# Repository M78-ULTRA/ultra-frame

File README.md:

# ULTRA FRAME

Open source hardware and design files for a **leverless controller**— arcade-style input without a joystick gate, built for fighting games and anyone who prefers all-button layouts.

This repository is **work in progress**. KiCad projects, mechanical CAD, firmware, and documentation will land here as the design matures. Watch this space or star the repo if you want to follow along.

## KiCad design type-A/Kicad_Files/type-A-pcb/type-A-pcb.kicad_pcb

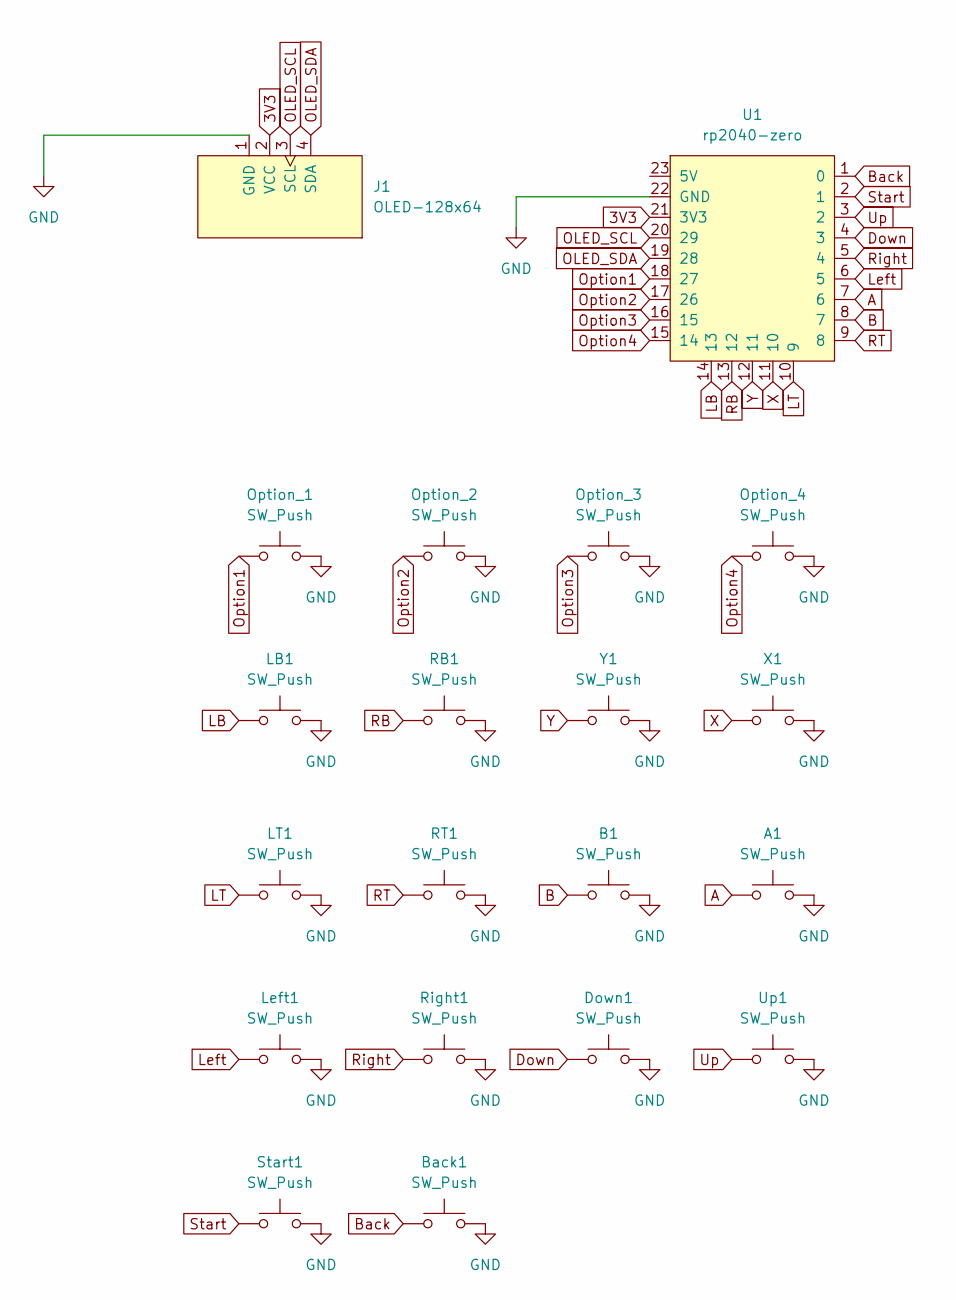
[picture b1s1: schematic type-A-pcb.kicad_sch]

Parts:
A1: SW_Push; Kailh_socket_PG1350_optional
B1: SW_Push; Kailh_socket_PG1350_optional
Back1: SW_Push; Kailh_socket_PG1350_optional
Down1: SW_Push; Kailh_socket_PG1350_optional
J1: OLED-128x64
LB1: SW_Push; Kailh_socket_PG1350_optional
LT1: SW_Push; Kailh_socket_PG1350_optional
Left1: SW_Push; Kailh_socket_PG1350_optional
Option_1, Option_2, Option_3, Option_4: SW_Push; Kailh_socket_PG1350_optional
RB1: SW_Push; Kailh_socket_PG1350_optional
RT1: SW_Push; Kailh_socket_PG1350_optional
Right1: SW_Push; Kailh_socket_PG1350_optional
Start1: SW_Push; Kailh_socket_PG1350_optional
U1: rp2040-zero; RP2040-Zero-Pretty
Up1: SW_Push; Kailh_socket_PG1350_optional
X1: SW_Push; Kailh_socket_PG1350_optional
Y1: SW_Push; Kailh_socket_PG1350_optional

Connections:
3V3: J1.2 (VCC), U1.21 (3V3)
A: A1.1, U1.7 (6)
B: B1.1, U1.8 (7)
Back: Back1.1, U1.1 (0)
Down: Down1.1, U1.4 (3)
GND: A1.2, B1.2, Back1.2, Down1.2, J1.1 (GND), LB1.2, LT1.2, Left1.2, Option_1.2, Option_2.2, Option_3.2, Option_4.2, RB1.2, RT1.2, Right1.2, Start1.2, U1.22 (GND), Up1.2, X1.2, Y1.2
LB: LB1.1, U1.14 (13)
LT: LT1.1, U1.10 (9)
Left: Left1.1, U1.6 (5)
OLED_SCL: J1.3 (SCL), U1.20 (29)
OLED_SDA: J1.4 (SDA), U1.19 (28)
Option1: Option_1.1, U1.18 (27)
Option2: Option_2.1, U1.17 (26)
Option3: Option_3.1, U1.16 (15)
Option4: Option_4.1, U1.15 (14)
RB: RB1.1, U1.13 (12)
RT: RT1.1, U1.9 (8)
Right: Right1.1, U1.5 (4)
Start: Start1.1, U1.2 (1)
Up: U1.3 (2), Up1.1
X: U1.11 (10), X1.1
Y: U1.12 (11), Y1.1

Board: 2 copper layers, 19 parts (0 on the bottom side), 19 nets, no tracks yet.

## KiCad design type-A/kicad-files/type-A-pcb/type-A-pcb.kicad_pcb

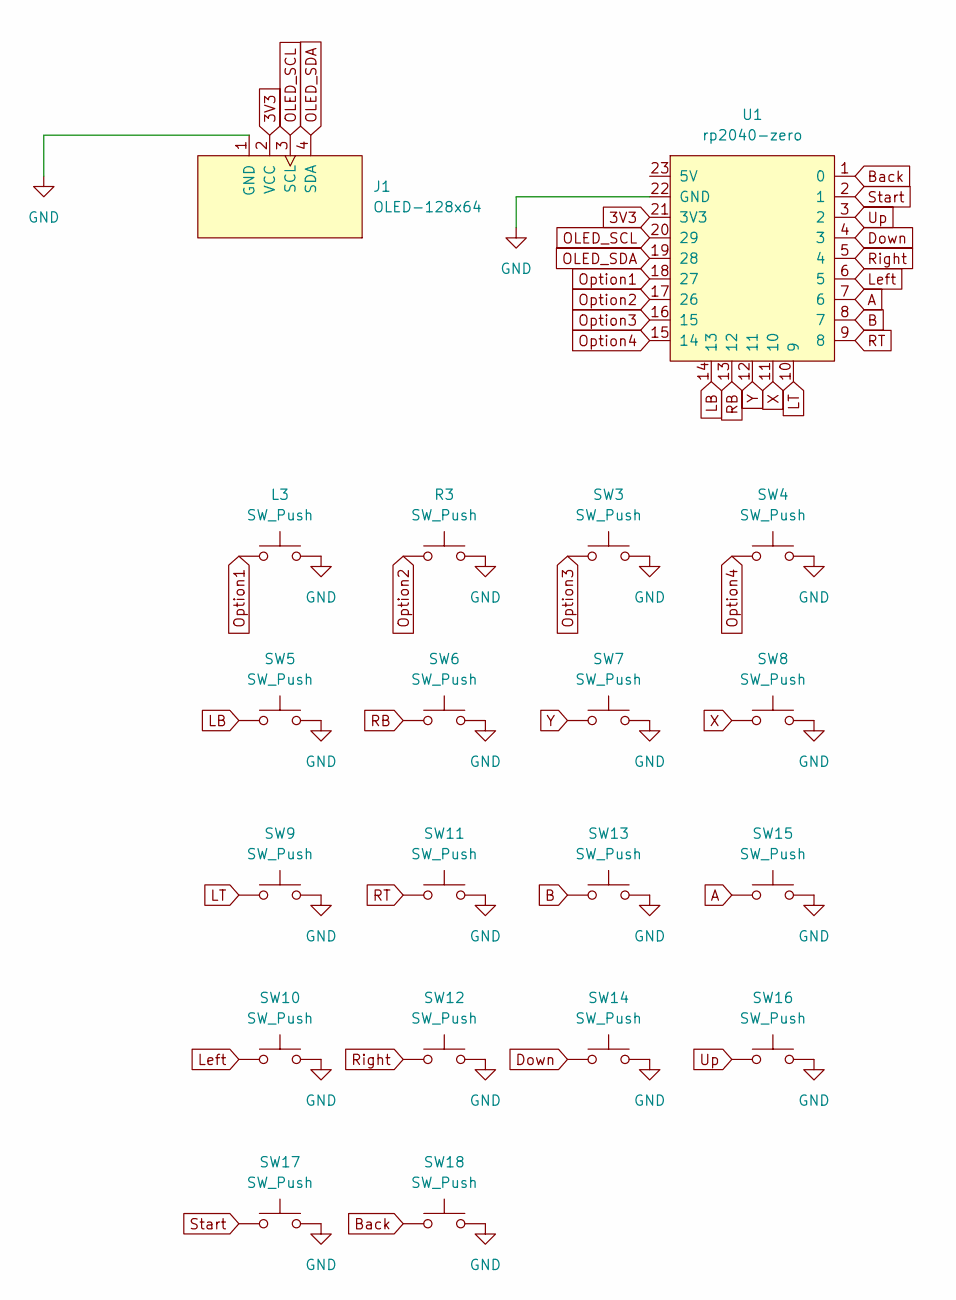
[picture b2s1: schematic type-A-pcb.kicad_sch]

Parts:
J1: OLED-128x64
L3: SW_Push; SW_Kailh_Choc_V1_1.00u
R3: SW_Push; SW_Kailh_Choc_V1_1.00u
SW3, SW4, SW5, SW6, SW7, SW8, SW9, SW10, SW11, SW12, SW13, SW14, SW15, SW16, SW17, SW18: SW_Push; SW_Kailh_Choc_V1_1.00u
U1: rp2040-zero; rp2040-zero-tht

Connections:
3V3: J1.2 (VCC), U1.21 (3V3)
A: SW15.1, U1.7 (6)
B: SW13.1, U1.8 (7)
Back: SW18.1, U1.1 (0)
Down: SW14.1, U1.4 (3)
GND: J1.1 (GND), L3.2, R3.2, SW3.2, SW4.2, SW5.2, SW6.2, SW7.2, SW8.2, SW9.2, SW10.2, SW11.2, SW12.2, SW13.2, SW14.2, SW15.2, SW16.2, SW17.2, SW18.2, U1.22 (GND)
LB: SW5.1, U1.14 (13)
LT: SW9.1, U1.10 (9)
Left: SW10.1, U1.6 (5)
OLED_SCL: J1.3 (SCL), U1.20 (29)
OLED_SDA: J1.4 (SDA), U1.19 (28)
Option1: L3.1, U1.18 (27)
Option2: R3.1, U1.17 (26)
Option3: SW3.1, U1.16 (15)
Option4: SW4.1, U1.15 (14)
RB: SW6.1, U1.13 (12)
RT: SW11.1, U1.9 (8)
Right: SW12.1, U1.5 (4)
Start: SW17.1, U1.2 (1)
Up: SW16.1, U1.3 (2)
X: SW8.1, U1.11 (10)
Y: SW7.1, U1.12 (11)

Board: 2 copper layers, 20 parts (0 on the bottom side), 22 nets, no tracks yet.

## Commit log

2026-03-31 Let's have some fun.
2026-03-31 Testing .gitignore
2026-03-31 Harden .gitignore for macOS and KiCad lock files
    Made-with: Cursor
2026-03-31 Testing changes.
2026-04-02 New Kicad library.
2026-04-06 New RP2040 Zero Footprint.
2026-04-06 Modified RP2040-Zero Footprint.
